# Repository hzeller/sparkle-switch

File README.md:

Sparkleswitch
=============

The Noisebridge Laser cutter is an expensive piece of machinery that has
some non-negligible running cost and requires some safety-training before use.

We require to authenticate with an RFID showing previous laser training
in order to switch the laser on. This project contains the relevant electronics
and software to build this switch.

We use a generic EStop/On/Off switch box ([Aliexpress][switch-box-ali], [Amazon][switch-box-amazon]) as basic user interface, coupled with an
additional [RFID reader].

## Requirements

 * Have a switch that provides on/off and emergency off buttons as well
   as an RFID reader.
 * The safety relevant triggering of the emergency button **must**
   shut off power reliably by simple electromechanical means with no software
   involved to work even if the computer has issues.
   After an Emergency-Off, it is required to reset the EStop button
   (manual twisting) _and_ re-activating via RFID.
 * Have a display to show the currently active user, potentially laser
   time accounting, uplifting idle-animations etc.
 * It is common to pass the custody of the running laser cutter to the next
   user, so make it simple to switch the active user without power-cycling
   the laser.
 * Connection between Pi and emergency off button is separate, so it should
   be simple to wire up.

## Design considerations

As controlling computer, we use a Raspberry Pi: it is cheap, [can run
a LED display][rpi-rgb-matrix], and has enough additional GPIO pins to
read button state and trigger relays.

Since we need to switch line voltage with the Pi, we use a relay.
The basic switch mechanism is a simple relay circuit acting as a Set/Reset
Flip-Flop that fails safe on power loss.
Two control relays for set/reset are triggered by the Raspberry Pi; the main
switching 4-pole relay is part of the flip-flop and also switching the
mains phases for the machine.

The mains relay uses one of its poles to act as self-sustaining relay.
A momentary switch of the 'on' trigger relay will switch on the machine,
and a momentary interrupt from the 'off' trigger will switch off the machine:

The Emergency-Off button is cutting power to the relay circuit, thus acting
as master reset (thereby meeting the no-software-involved safety requirements).
Set (= switch power on) and Reset (= switch power off) are triggered by the
Raspberry Pi.

Inputs and outputs are

 * `in` **Emergency Off** button. Directly wired in the
    circuit acting as physical 'reset' for the SR-FlipFlop. Also wired to a
    GPIO as input to inform the application about the state.
 * `in` **On** button. Wired to a GPIO input as a soft-button for
    the application.
 * `in` **Off** button. Wired to a GPIO input as a soft-button for the
    application.
 * `in` a sense input to detect if the mains-relay coil voltage is on. Mostly
    for fault detection via software.
 * `out` **Trigger on** relay. Controlled by GPIO
    to trigger *set* of SR-FlipFlop.
 * `out` **Trigger off** relay. Controlled by GPIO
    to trigger *reset* of SR-FlipFlop.
 * `serial in/out` **RFID** reader (connected to UART on Pi).

Since we use the on/off buttons to interact with the application as
soft-buttons (e.g. to trigger 'pending off'), they are not physically wired
into the circuit but used as input to the computer (this is fine as they
are not in the safety critical path).

There is a little space in the switch box which will house the trigger relays
and possibly the RFID reader. The relay switching of the line voltage for the
laser cutter is mounted near the outlet for the machine, connected with three
wires (see above:`GND`, `Sustain`, `Trigger ON`) remotely from the switch box.

As trigger relays, we use off-the-shelf and [cheap][ebay-search-dual-relay]
relays.

## State machine

The software on the Pi implements the following state machine; it uses inputs
and outputs mentioned above.
Inputs are on the transition edges; external actions triggered by the
application are represented as hexagons. Since we often have the situation
that we want to pass the running laser to the next user without having to
switch it entirely off and on again, there is a provision to change the user
while the machine is running:

## Components

There are three physical parts to the system:

  1. RGB LED matrix screen, that has a Raspberry Pi connected to it to
     display the user interface.
  2. The switch box is separate from that and mounted under the display.
  3. The mains relay that is close to the outlet of the
     laser-cutter, and remotely controlled with a 12V control voltage.

The connection between the switch-box and the Pi is a simple flat cable with
an [IDC-12 connector] on both ends.

| Desc               | Pin | Pin | Desc
|-------------------:|:---:|:---:|:-----------------------------
|               +5V  |   1 |   2 | +5V (low current; for trigger relays and RFID)
|   Sense EStop `in` |   3 |   4 | `in` sense relay voltage (e.g. for failure detection)
|    Off-Button `in` |   5 |   6 | `out` Relay Trigger Off
|     On-Button `in` |   7 |   8 | `out` Relay Trigger On
|               GND  |   9 |  10 | GND
|     UART RX on Pi  |  11 |  12 | UART TX on Pi (3.3V TTL)

There is a PCB on the Raspberry Pi to wire up the LED panels and provide the
connector to the switch-box, and a PCB in the switch-box as a breakout board.

### Pi Sparkle HAT

The Rasbperry Pi connects to the [Pi Sparkle HAT](./hardware/pi-hat), that
provides connections for two chains of HUB75 RGB LED matrix
(using the [rpi-rgb-matrix] project) and the
Sparkleswitch-specific IDC-12 connector to connect to the switch box.

Inputs (from switches and sense-lines all operating at 12V) are insulated with
opto couplers. The relay trigger outputs are 5V TTL
(but non-insulated as the receiving end uses opto-couplers already).

### Switch Box

A [small breakout board in the switch-box](./hardware/switch-connector)
provides a way to connect the switches, the Trigger-Relays (housed inside the
switch-box) and the RFID reader (attached to switch box). It also provides a
screw terminal to wire up to the mains-relay whose wires are also terminating
in the switch box.

[switch-box-ali]: https://www.aliexpress.com/wholesale?SearchText=NC+Emergency+Stop+Red+Green
[switch-box-amazon]: https://www.amazon.com/gp/product/B0097B4YK0
[rpi-rgb-matrix]: https://github.com/hzeller/rpi-rgb-led-matrix
[RFID reader]: https://github.com/noisebridge/rfid-access-control/tree/master/hardware/terminal
[IDC-12 Connector]: https://www.google.com/images?q=idc-12+connector
[ebay-search-dual-relay]: https://www.ebay.com/sch/i.html?_nkw=%222+channel%22+relay+arduino&_sop=15

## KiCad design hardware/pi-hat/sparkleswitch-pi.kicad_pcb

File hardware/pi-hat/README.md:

Pi Sparkle HAT
==============

The Sparkle HAT connects to Raspberry Pi GPIOs, does 3.3V->5V level shifting
to connect to HUB75 LED matrixes (to be controlled with the [rpi-rgb-matrix]
code), and the Sparkleswitch-specific IDC-12 connector to connect to the
switch box.

The level shifters are needed as the LED matrixes need 5V logic level. We also
use two free drivers to provide 5V TTL level for the trigger relay outputs
on the IDC-12 connector.

Inputs (from switches and sense-lines all operating at 12V) are insulated with
PC817 opto couplers. The relay trigger outputs are non-insulated as the
receiving end uses opto-couplers already.

To provide strong mechanical support, the HAT is full size with all four
mounting holes.

[rpi-rgb-matrix]: https://github.com/hzeller/rpi-rgb-led-matrix

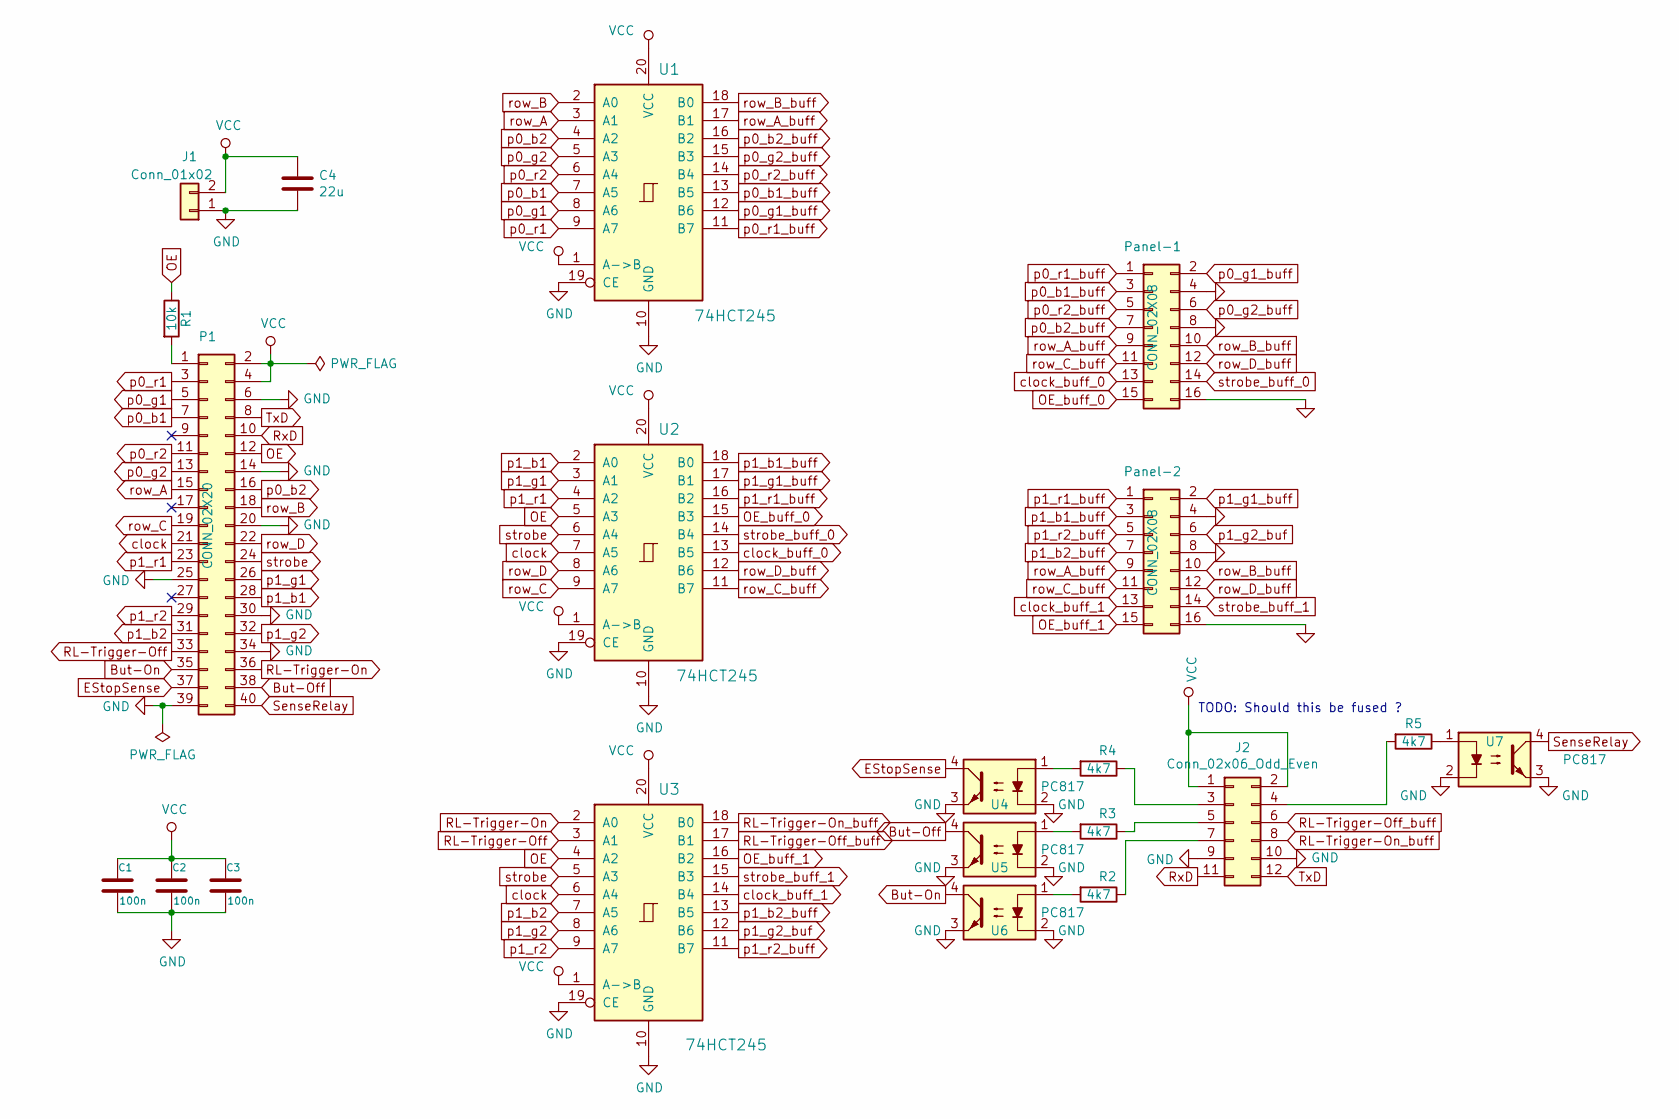
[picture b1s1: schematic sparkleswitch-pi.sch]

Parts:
C1, C2, C3: 100n; C_0603
C4: 22u; C_1210
J1: Conn_01x02; TerminalBlock_4UCON_19963_02x3.5mm_Straight
J2: Conn_02x06_Odd_Even; IDC-Header_2x06_Pitch2.54mm_Straight
P1: CONN_02X20; Socket_Strip_Straight_2x20_Pitch2.54mm
Panel-1, Panel-2: CONN_02X08; IDC-Header_2x08_Pitch2.54mm_Straight
R1: 10k; R_0603
R2, R3, R4, R5: 4k7; R_0603
U1, U2, U3: 74HCT245; SSOP-20_4.4x6.5mm_Pitch0.65mm
U4, U5, U6, U7: PC817; DIP-4_W7.62mm

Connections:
But-Off: P1.38, U5.4
But-On: P1.35, U6.4
EStopSense: P1.37, U4.4
GND: C1.2, C2.2, C3.2, C4.2, J1.1, J2.9, J2.10, P1.6, P1.14, P1.20, P1.25, P1.30, P1.34, P1.39, Panel-1.4, Panel-1.8, Panel-1.16, Panel-2.4, Panel-2.8, Panel-2.16, U1.10 (GND), U1.19 (CE), U2.10 (GND), U2.19 (CE), U3.10 (GND), U3.19 (CE), U4.2, U4.3, U5.2, U5.3, U6.2, U6.3, U7.2, U7.3
unnamed: J2.3, R4.1
unnamed: J2.4, R5.2
unnamed: J2.5, R3.1
unnamed: J2.7, R2.1
unnamed: P1.1, R1.2
unnamed: R2.2, U6.1
unnamed: R3.2, U5.1
unnamed: R4.2, U4.1
unnamed: R5.1, U7.1
OE: P1.12, R1.1, U2.5 (A3), U3.4 (A2)
OE_buff_0: Panel-1.15, U2.15 (B3)
OE_buff_1: Panel-2.15, U3.16 (B2)
RL-Trigger-Off: P1.33, U3.3 (A1)
RL-Trigger-Off_buff: J2.6, U3.17 (B1)
RL-Trigger-On: P1.36, U3.2 (A0)
RL-Trigger-On_buff: J2.8, U3.18 (B0)
RxD: J2.11, P1.10
SenseRelay: P1.40, U7.4
TxD: J2.12, P1.8
VCC: C1.1, C2.1, C3.1, C4.1, J1.2, J2.1, J2.2, P1.2, P1.4, U1.1 (A->B), U1.20 (VCC), U2.1 (A->B), U2.20 (VCC), U3.1 (A->B), U3.20 (VCC)
clock: P1.21, U2.7 (A5), U3.6 (A4)
clock_buff_0: Panel-1.13, U2.13 (B5)
clock_buff_1: Panel-2.13, U3.14 (B4)
p0_b1: P1.7, U1.7 (A5)
p0_b1_buff: Panel-1.3, U1.13 (B5)
p0_b2: P1.16, U1.4 (A2)
p0_b2_buff: Panel-1.7, U1.16 (B2)
p0_g1: P1.5, U1.8 (A6)
p0_g1_buff: Panel-1.2, U1.12 (B6)
p0_g2: P1.13, U1.5 (A3)
p0_g2_buff: Panel-1.6, U1.15 (B3)
p0_r1: P1.3, U1.9 (A7)
p0_r1_buff: Panel-1.1, U1.11 (B7)
p0_r2: P1.11, U1.6 (A4)
p0_r2_buff: Panel-1.5, U1.14 (B4)
p1_b1: P1.28, U2.2 (A0)
p1_b1_buff: Panel-2.3, U2.18 (B0)
p1_b2: P1.31, U3.7 (A5)
p1_b2_buff: Panel-2.7, U3.13 (B5)
p1_g1: P1.26, U2.3 (A1)
p1_g1_buff: Panel-2.2, U2.17 (B1)
p1_g2: P1.32, U3.8 (A6)
p1_g2_buf: Panel-2.6, U3.12 (B6)
p1_r1: P1.23, U2.4 (A2)
p1_r1_buff: Panel-2.1, U2.16 (B2)
p1_r2: P1.29, U3.9 (A7)
p1_r2_buff: Panel-2.5, U3.11 (B7)
row_A: P1.15, U1.3 (A1)
row_A_buff: Panel-1.9, Panel-2.9, U1.17 (B1)
row_B: P1.18, U1.2 (A0)
row_B_buff: Panel-1.10, Panel-2.10, U1.18 (B0)
row_C: P1.19, U2.9 (A7)
row_C_buff: Panel-1.11, Panel-2.11, U2.11 (B7)
row_D: P1.22, U2.8 (A6)
row_D_buff: Panel-1.12, Panel-2.12, U2.12 (B6)
strobe: P1.24, U2.6 (A4), U3.5 (A3)
strobe_buff_0: Panel-1.14, U2.14 (B4)
strobe_buff_1: Panel-2.14, U3.15 (B3)

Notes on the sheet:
TODO: Should this be fused ?

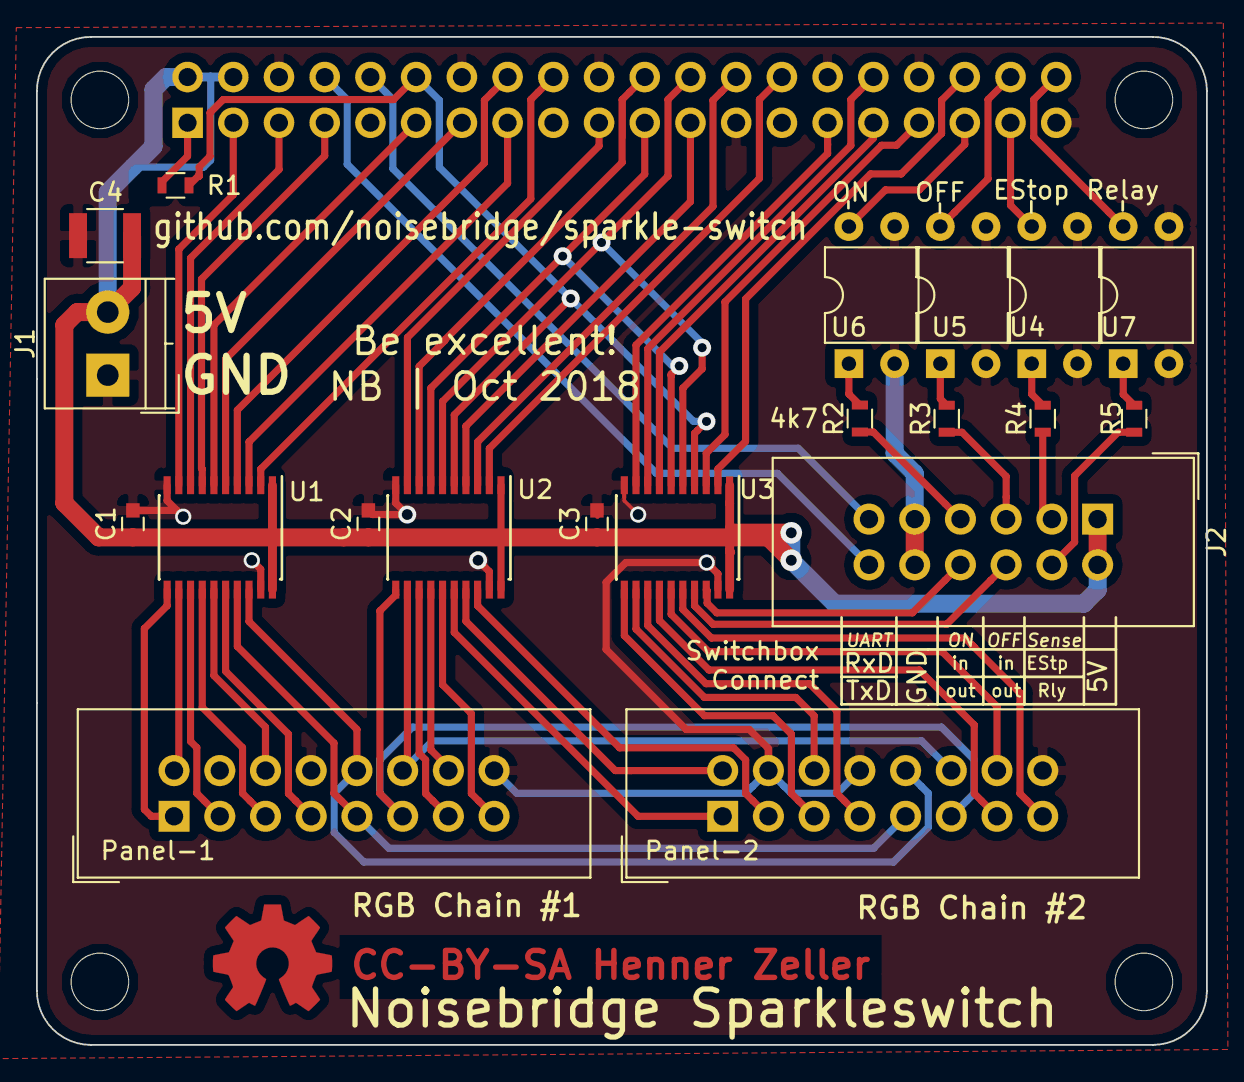
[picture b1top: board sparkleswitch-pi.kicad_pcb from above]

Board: 2 copper layers, 65.0 x 56.0 mm, 21 parts (1 on the bottom side), 62 nets.

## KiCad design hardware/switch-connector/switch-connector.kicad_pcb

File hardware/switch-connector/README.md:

Switch Connector
================

The IDC-12 cable from the Raspberry Pi terminates inside the switch box.

There, it needs to connect to

   * The RFID reader via the serial interface.
   * Switches to sense which buttons are pressed (sent to Pi).
   * EStop button that is wired up as physical master-reset of the
     relay Set/Reset flip-flop. Also its state is sensed and sent to
     Pi to detect that condition in software.
   * Trigger relay inputs, controlled from the Pi.
   * The trigger relay switches, that are part of the Set/Reset flip-flop
   * And finally: the wires to the large mains relay.

To simplify that and improve maintainability, this is a small PCB inside the
switch box that provides the necessary connectors.

The IDC-12 connector has the following pinout:

| Desc               | Pin | Pin | Desc
|-------------------:|:---:|:---:|:-----------------------------
|               +5V  |   1 |   2 | +5V (low current; for trigger relays and RFID)
|   Sense EStop `in` |   3 |   4 | `in` sense relay voltage (e.g. for failure detection)
|    Off-Button `in` |   5 |   6 | `out` Relay Trigger Off
|     On-Button `in` |   7 |   8 | `out` Relay Trigger On
|               GND  |   9 |  10 | GND
|     UART RX on Pi  |  11 |  12 | UART TX on Pi (3.3V TTL)

The connector to the On/Off/EStop switches is a 6 pos JST-XH connector,
which can be cheaply acquired pre-crimped, as they are also used as
battery charge balance connectors.

The connectors to the [RFID reader], and the input to the trigger relay are
also JST connectors. The former uses JST-XH (2.5mm pitch), the latter
JST-PH (2mm pitch) to avoid wrong wirings.

As trigger relay, simple generic dual relays are used, that are super-cheap
[on ebay][ebay-search-dual-relay]

## Schematic and Board

[RFID Reader]: https://github.com/noisebridge/rfid-access-control/tree/master/hardware/terminal
[ebay-search-dual-relay]: https://www.ebay.com/sch/i.html?_nkw=%222+channel%22+relay+arduino&_sop=15

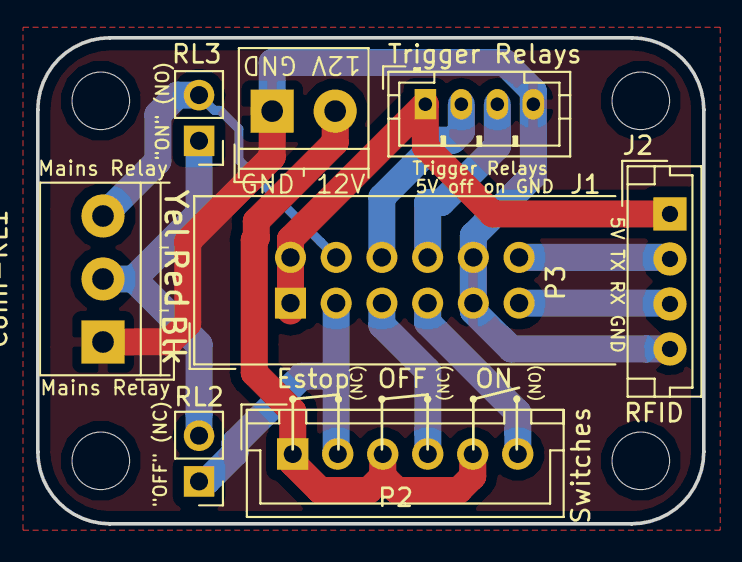
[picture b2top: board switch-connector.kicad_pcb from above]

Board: 2 copper layers, 37.0 x 27.0 mm, 8 parts (0 on the bottom side), 12 nets.

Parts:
Conn-RL1: HV-Relay; TerminalBlock_4UCON_19963_03x3.5mm_Straight
J1: Relay Control; JST_PH_B4B-PH-K_04x2.00mm_Straight
J2: RFID connect; JST_EH_B04B-EH-A_04x2.50mm_Straight
P1: 12V; TerminalBlock_4UCON_19963_02x3.5mm_Straight
P2: Switches; JST_XH_B06B-XH-A_06x2.50mm_Straight
P3: Pi; IDC-Header_2x06_Pitch2.54mm_Straight
RL2: Trigger off (NC); Pin_Header_Straight_1x02_Pitch2.54mm
RL3: Enable On (NO); Pin_Header_Straight_1x02_Pitch2.54mm

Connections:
+5V: J1.1, J2.1, P3.1, P3.2
+12V: P1.2, P2.1, P2.3, P2.5
/Sustain: Conn-RL1.2, RL2.2, RL3.1
/Trigger: Conn-RL1.3, P3.4, RL3.2
/switch-box/But-Off: P2.4, P3.5
/switch-box/But-On: P2.6, P3.7
/switch-box/RL-Trigger-Off: J1.2, P3.6
/switch-box/RL-Trigger-On: J1.3, P3.8
/switch-box/RX: J2.3, P3.11
/switch-box/Sense-EStop: P2.2, P3.3, RL2.1
/switch-box/TX: J2.2, P3.12
GND: Conn-RL1.1, J1.4, J2.4, P1.1, P3.9, P3.10

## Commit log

2016-08-27 o Initial set of files
2016-08-27 o Fix sizes.
2017-02-20 o Submit switch connector.
2017-02-20 o make hierarchical sheet.
2017-02-20 New local parts lib with quad-pole relay.
2017-02-20 o Update board with new connectors.
2017-02-20 o Add basic scripts to generate fab outputs.
2017-02-21 o tweaks.
2017-02-21 o Add relay to the toplevel schematic
2017-02-21 o clarifications in schematic
2017-12-29 Upgrade to new eeschema lib.
2017-12-29 symbol library references needed.
2017-12-29 A little more silkscreen to ease assembly.
    Also:
    o enough space for actual connectors for switches and sense outputs
    o have inputs for every single switch ('eStop' and 'off' were sharing one)
2017-12-29 Rounded corners.
2017-12-29 Add screw terminal for 12V
2018-01-01 Add a generic relay for illustration schematics.
2018-01-06 Some tweaking (but about to be changed for refined design)
2018-01-06 Start documentation.
2018-01-06 Update schematic to refined design.
    (PCB still needs to be adapted)
2018-01-06 Add stub README for switch-connector.
2018-01-06 Use IDC-12 for lower impedance 5V/GND connection.
    The flat cable might be a meter or so long, the 5V relays might need
    some current and the strands are flimsy.
    Also, better separation of the 12V-ish logic and the RX/TX wiring.
2018-01-06 Exclude mouse cursor in schematic screenshot.
2018-01-06 Fix typo in README. Wire a signal directly (instead of labels) where possible.
2018-01-16 Also provide an Aliexpress link as the Amazon offer seems to be unavailable at times.
2018-10-23 First version of the PCB using the IDC connector.
2018-10-23 Update Schematic image in README; smallish tweaks in PCB.
2018-10-23 Update README with clarifications; add switch-box PCB rendering.
2018-10-23 Show front and back of box-switch pcb.
2018-10-23 Upate README with the new pinout.
2018-10-23 Start hat for Pi to control LED panels and switch box.
2018-10-24 First wiring up with somewhat minimized via count.
    This required to rewire GPIOs a little, but since this is a specific
    set-up anyway.
2018-10-24 First version with all connections.
2018-10-24 Clarify swapping user in on-state.
2018-10-24 Make traces thicker as we have the space.
    o Increase size of traces from 0.25mm to 0.4mm as space is
    not that constricted (right now only the afferent traces).
2018-10-24 Thicker efferent traces.
2018-10-24 More space between Led Matrix HUB75 IDC connectors.
    .. to make sure they don't physically interfere.
2018-10-24 Center middle '245
2018-10-24 Add helpful silkscreen markings.
2018-10-24 Update documentation.
2018-10-24 Add missing images.
2018-10-25 More detailed description in RS-flip-flop illustration.
2018-10-25 More relay flip-flop illustration tweaks.
2018-12-23 Use 4.7k for OptoCoupler LEDs; OE-Pullup 0805 -> 0603

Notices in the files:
hardware/pi-hat/sparkleswitch-pi.kicad_pcb:
CC-BY-SA Henner Zeller
